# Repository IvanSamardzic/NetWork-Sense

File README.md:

## NetWork-Sense

* Low Power Consumption
* Energy Autonomy
* Wireless Communication Realisation Using Radio Vawes

### System Architecture

#### Arduino Nano Pin Configuration

```
const int redLed = 2;
const int greenLed = 3;
const int cePin = 7;
const int csnPin = 8;
const int trigPin = 9;
const int echoPin = 10;
const int mosiPin = 11;
const int misoPin = 12;
const int sckPin = 13;
```

#### ESP32 Pin Configuration

```
const int cePin = 4;
const int csnPin = 5;
const int mosiPin = 23;
const int misoPin = 19;
const int sckPin = 18;
```

#### Network Explanation

The node has the function of monitoring the presence of the object at an angle of 45 degrees, when the vessel / vehicle is recognized by a sensor, then this status change
message is sent to the main node of the sensor network (gateway) using a radio module operating at 2.4 GHz.

When the master node receives a state change message on one of its child nodes, then the gateway sends a request to the database to change the value that determines the
occupancy of the position in front of the sensor.

###### Connection to WiFi Network
```
WiFi.begin(ssid, password);
    Serial.println("Connecting");
    while (WiFi.status() != WL_CONNECTED) {
    delay(500);
    Serial.print(".");
    }
    Serial.println("");
    Serial.print("Connected to WiFi network with IP Address: ");
    Serial.println(WiFi.localIP());
    Serial.println();
    Serial.println();
    Serial.println();
}
```
The gateway is equipped with an ESP32 microcontroller that has the ability to connect to a WiFi network, communicates with the database by sending various HTTP requests.The
ability to send HTTP requests is possible if the HTTP Client is properly created to receive and send data to the HTTP Server.

###### HTTP Client Initialisation 
```
//Send an HTTP POST request every 10 minutes
    if ((millis() - lastTime) > timerDelay) {
    //Check WiFi connection status
    if (WiFi.status() == WL_CONNECTED) {
      HTTPClient http;
    }
    else {
      Serial.println("WiFi Disconnected");
    }
    // Measure the time the system tries to create HTTP Client or
    // time it has been created
    lastTime = millis();
    // Wait for 2000msec
    delay(2000);
  }

```

###### Sensor Data Acquisition And Conversion Into String

```
  digitalWrite(trigPin, LOW);
  delayMicroseconds(delayPeriod/5);
  digitalWrite(trigPin, HIGH);
  delayMicroseconds(delayPeriod);
  digitalWrite(trigPin, LOW);
  duration = pulseIn(echoPin, HIGH);
  distance = duration * conversionFactor;
  Serial.print("Distance: ");
  Serial.println(distance);
  if(distance < distanceLevel){
    digitalWrite(redLed, HIGH);
    digitalWrite(greenLed, LOW);
    isTaken = true;
  }
  else{
    digitalWrite(redLed, LOW);
    digitalWrite(greenLed, HIGH);
    isTaken = false;
  }
```

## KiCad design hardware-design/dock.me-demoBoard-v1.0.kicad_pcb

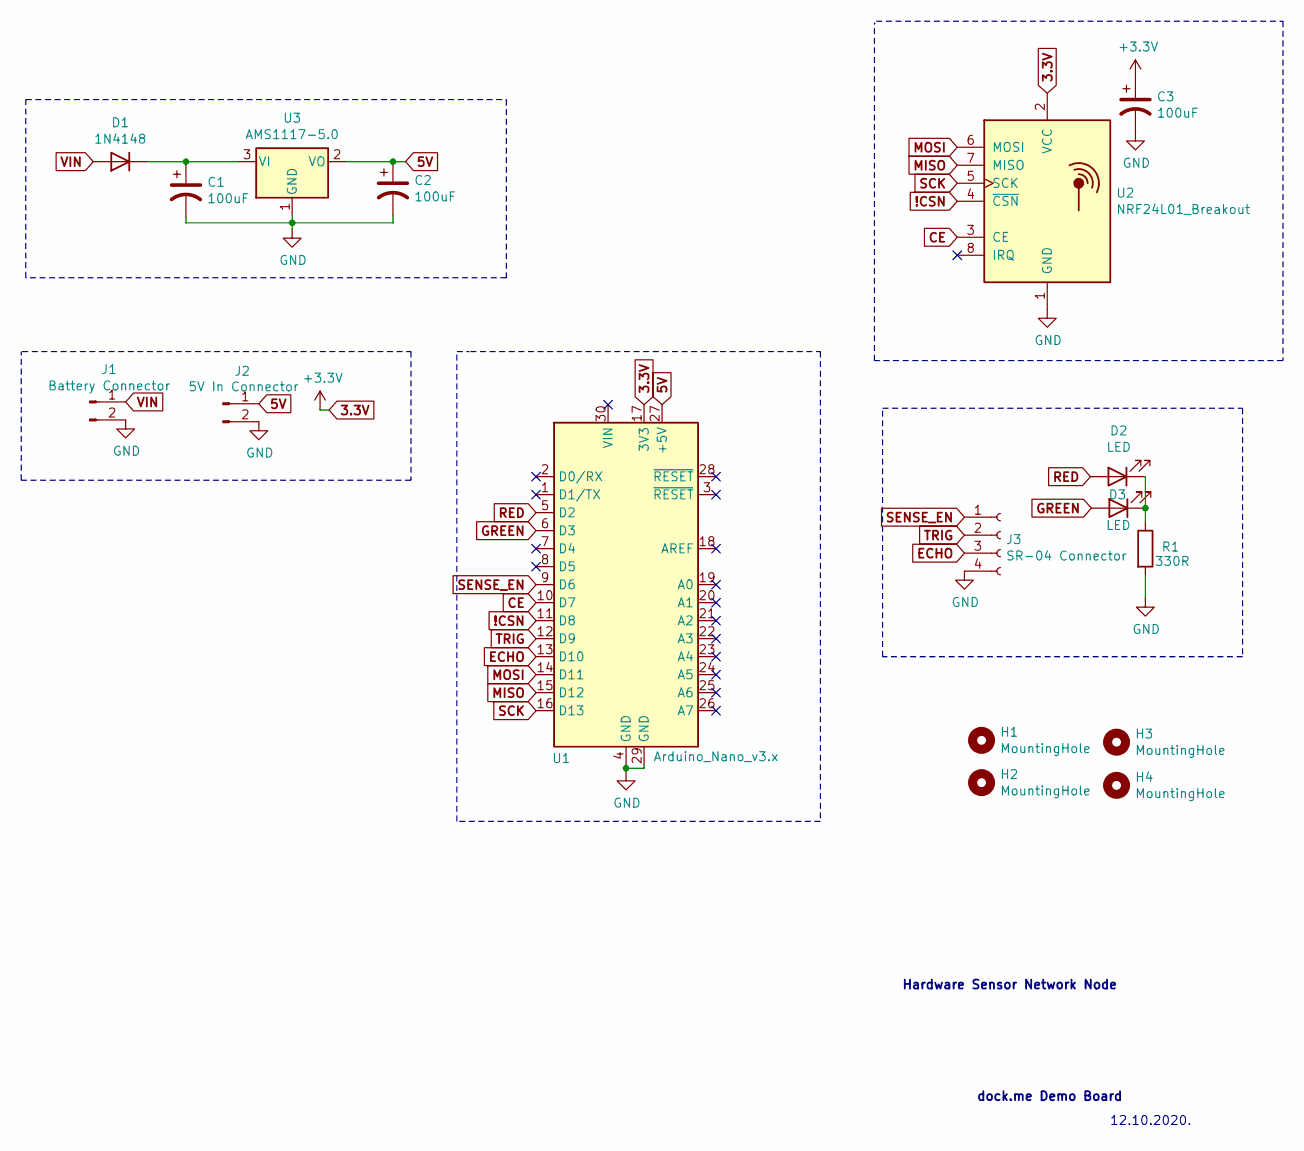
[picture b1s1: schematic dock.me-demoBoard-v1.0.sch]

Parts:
C1, C2, C3: 100uF; CP_Radial_D4.0mm_P1.50mm
D1: 1N4148; D_DO-35_SOD27_P7.62mm_Horizontal
D2, D3: LED; LED_D5.0mm
H1, H2, H3, H4: MountingHole; MountingHole_2.5mm
J1: Battery Connector; 1x02_5.08mm
J2: 5V In Connector; 1x02_5.08mm
J3: SR-04 Connector; PinSocket_1x04_P2.54mm_Vertical
R1: 330R; R_Axial_DIN0414_L11.9mm_D4.5mm_P15.24mm_Horizontal
U1: Arduino_Nano_v3.x; Arduino_Nano
U2: NRF24L01_Breakout; nRF24L01_Breakout
U3: AMS1117-5.0; SOT-223-3_TabPin2

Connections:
3.3V: C3.1, U1.17 (3V3), U2.2 (VCC)
5V: C2.1, J2.1, U1.27 (+5V), U3.2 (VO)
!CSN: U1.11 (D8), U2.4 (~CSN)
CE: U1.10 (D7), U2.3 (CE)
ECHO: J3.3, U1.13 (D10)
GND: C1.2, C2.2, C3.2, J1.2, J2.2, J3.4, R1.2, U1.4 (GND), U1.29 (GND), U2.1 (GND), U3.1 (GND)
GREEN: D3.2 (A), U1.6 (D3)
MISO: U1.15 (D12), U2.7 (MISO)
MOSI: U1.14 (D11), U2.6 (MOSI)
unnamed: C1.1, D1.1 (K), U3.3 (VI)
unnamed: D2.1 (K), D3.1 (K), R1.1
RED: D2.2 (A), U1.5 (D2)
SCK: U1.16 (D13), U2.5 (SCK)
SENSE_EN: J3.1, U1.9 (D6)
TRIG: J3.2, U1.12 (D9)
VIN: D1.2 (A), J1.1

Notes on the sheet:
dock.me Demo Board
12.10.2020.
Hardware Sensor Network Node

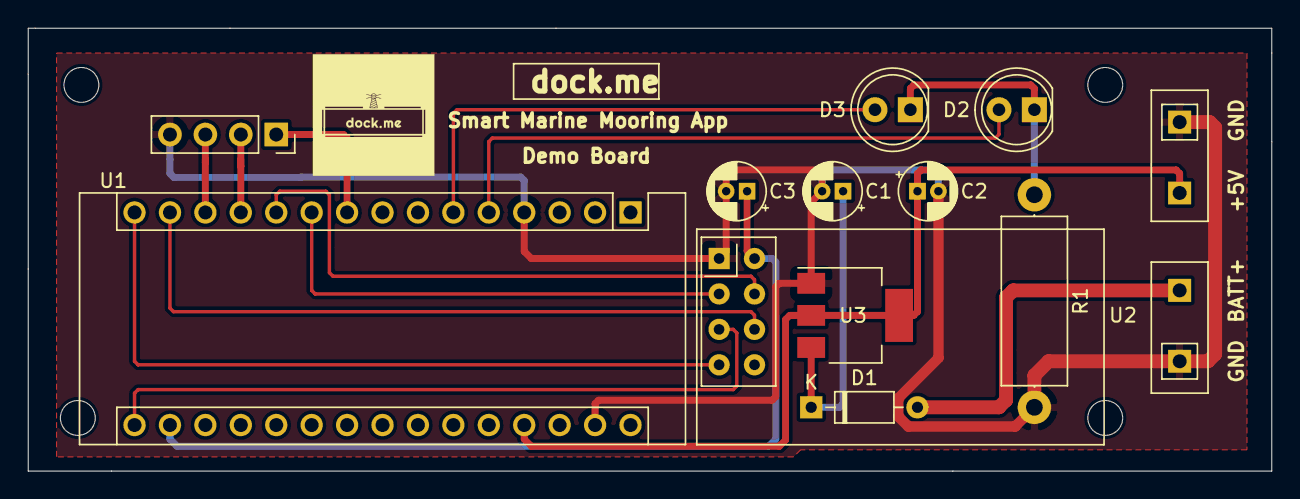
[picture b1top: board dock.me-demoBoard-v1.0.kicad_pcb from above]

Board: 2 copper layers, 89.2 x 31.8 mm, 17 parts (0 on the bottom side), 16 nets.

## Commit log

2020-11-21 Hello World sending and receiving
2020-11-21 Increment number sending and receiving
